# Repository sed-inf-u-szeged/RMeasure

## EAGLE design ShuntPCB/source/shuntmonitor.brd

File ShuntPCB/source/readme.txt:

PCB design sources, made with Eagle 7.2.0.

- shubtmonitor.sch: Schematic
- shubtmonitor.brd: Board

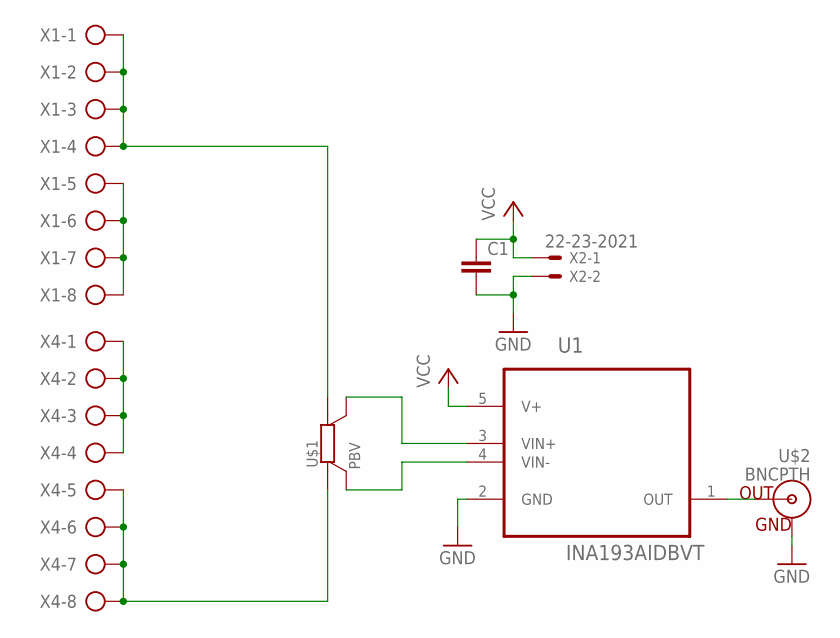
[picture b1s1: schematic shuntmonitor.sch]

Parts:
C1: C-EUC0805; C0805
U1: INA193AIDBVT; SOT95P280X145-5N
U$1: PBV
U$2: BNCPTH; BNC
X1, X4: AK500/8
X2: 22-23-2021

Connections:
GND: C1.2, U1.2 (GND), U$2.GND, X2.2
unnamed: X4.1, X4.2, X4.3, X4.4
unnamed: U1.1 (OUT), U$2.S (OUT)
unnamed: U1.4 (VIN-), U$1.U2 (SB)
unnamed: U1.3 (VIN+), U$1.U1 (SA)
unnamed: U$1.I2 (B), X4.5, X4.6, X4.7, X4.8
unnamed: X1.5, X1.6, X1.7, X1.8
unnamed: U$1.I1 (A), X1.1, X1.2, X1.3, X1.4
VCC: C1.1, U1.5 (V+), X2.1

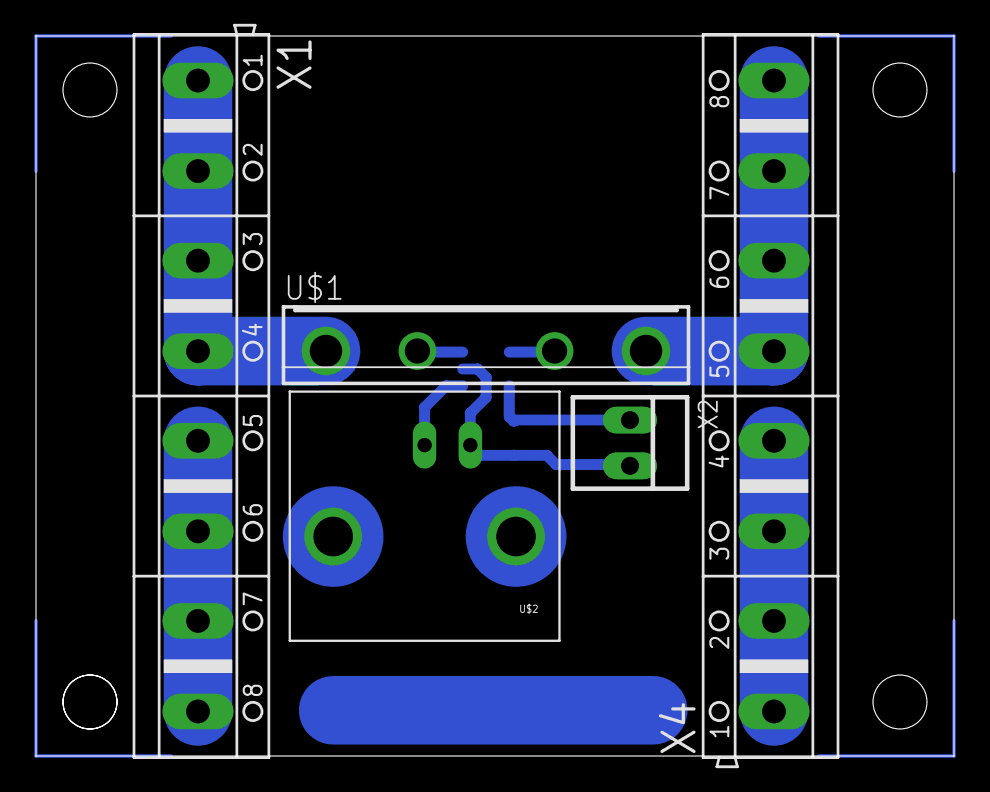
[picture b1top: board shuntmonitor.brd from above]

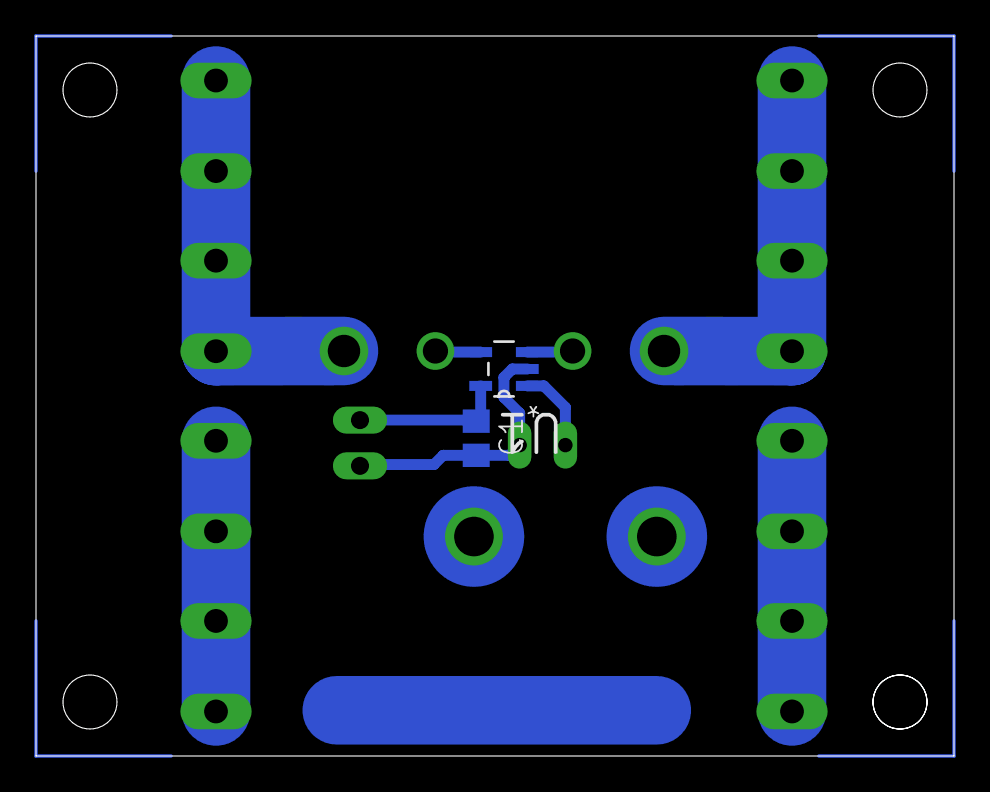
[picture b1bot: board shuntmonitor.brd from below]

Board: 2 copper layers, 51.0 x 40.0 mm, 7 parts (2 on the bottom side), 9 nets.

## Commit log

2017-08-10 Initial GitHub release of RMeasure

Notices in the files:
parts and their libraries:
SparkFun-Connectors: Licensing: Creative Commons ShareAlike 4.0 International - https://creativecommons.org/licenses/by-sa/4.0
